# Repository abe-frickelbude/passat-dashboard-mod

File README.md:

# Utilities for the VW Passat (3BG) instrument panel backlight modification project

## adc-serial-monitor

* Written with SpringBoot and Swing
* Provides:
  * A basic "oscilloscope" for AVR ADC input visualization along with some simple signal filtering options
  * A visual controller for RGB(W) programmable LED strips

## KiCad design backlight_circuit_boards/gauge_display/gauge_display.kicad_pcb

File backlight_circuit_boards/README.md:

# Passat 3BG instrument panel backlight circuits

## Center gauge backlight

* Consists of 4x SK6812 RGBW LEDs along with decoupling capacitors
* Custom board, fits existing compartment in the instrument panel's "light mask"
* The DXF file contains the board outline

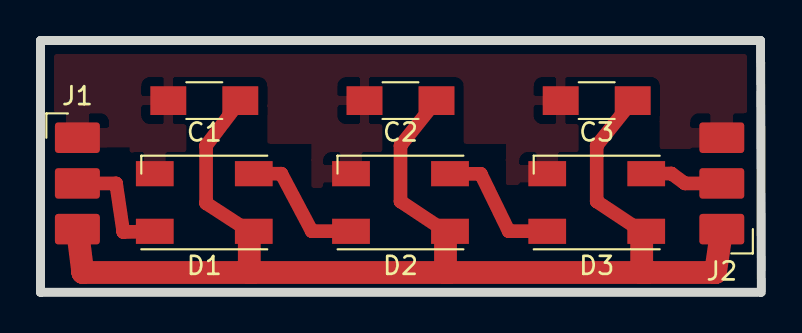
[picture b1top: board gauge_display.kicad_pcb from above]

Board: 2 copper layers, 40.0 x 14.0 mm, 8 parts (0 on the bottom side), 6 nets.

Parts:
C1, C2, C3: C; C_1206_HandSoldering
D1, D2, D3: WS2812B; LED_WS2812B-PLCC4_HandSoldering
J1, J2: Conn_01x03; wire_solder_pads_1x03_2.5x1.7mm_Pitch2.54mm

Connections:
GND: C1.2, C2.2, C3.2, D1.3, D2.3, D3.3, J1.1, J2.3
unnamed: D1.2, D2.4
unnamed: D1.4, J1.2
unnamed: D2.2, D3.4
unnamed: D3.2, J2.2
VCC: C1.1, C2.1, C3.1, D1.1, D2.1, D3.1, J1.3, J2.1

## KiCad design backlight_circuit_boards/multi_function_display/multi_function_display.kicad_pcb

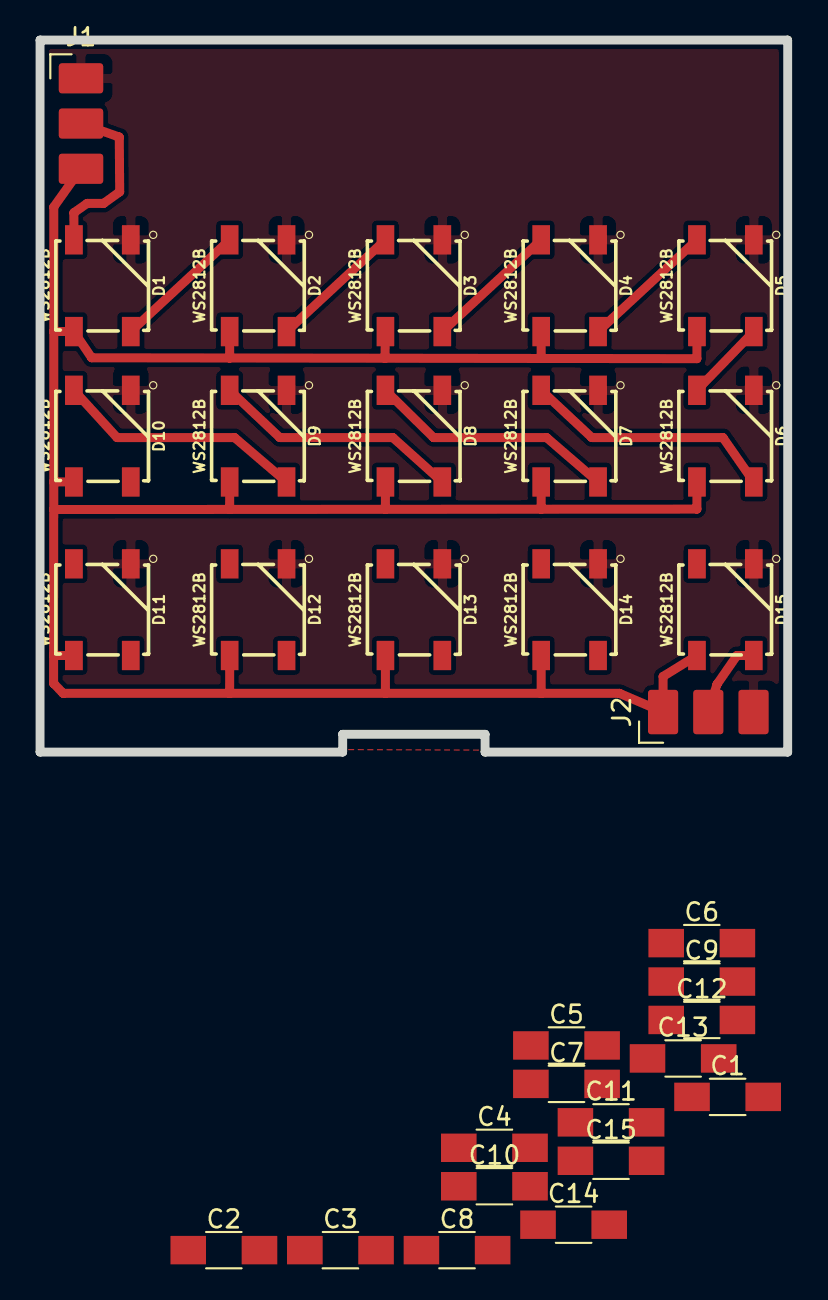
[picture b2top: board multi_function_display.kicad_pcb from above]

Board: 2 copper layers, 42.0 x 40.0 mm, 32 parts (0 on the bottom side), 18 nets.

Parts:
C1, C2, C3, C4, C5, C6, C7, C8, C9, C10, C11, C12, C13, C14, C15: 0.1; C_1206_HandSoldering
D1, D2, D3, D4, D5, D6, D7, D8, D9, D10, D11, D12, D13, D14, D15: WS2812B
J1, J2: Conn_01x03; wire_solder_pads_1x03_2.5x1.7mm_Pitch2.54mm

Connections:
GND: C1.2, C2.2, C3.2, C4.2, C5.2, C6.2, C7.2, C8.2, C9.2, C10.2, C11.2, C12.2, C13.2, C14.2, C15.2, D1.3, D2.3, D3.3, D4.3, D5.3, D6.3, D7.3, D8.3, D9.3, D10.3, D11.3, D12.3, D13.3, D14.3, D15.3, J1.1, J2.3
unnamed: D1.2, D2.4
unnamed: D1.4, J1.2
unnamed: D2.2, D3.4
unnamed: D3.2, D4.4
unnamed: D4.2, D5.4
unnamed: D5.2, D6.4
unnamed: D6.2, D7.4
unnamed: D7.2, D8.4
unnamed: D8.2, D9.4
unnamed: D10.2, D11.4
unnamed: D9.2, D10.4
unnamed: D11.2, D12.4
unnamed: D12.2, D13.4
unnamed: D13.2, D14.4
unnamed: D14.2, D15.4
unnamed: D15.2, J2.2
VCC: C1.1, C2.1, C3.1, C4.1, C5.1, C6.1, C7.1, C8.1, C9.1, C10.1, C11.1, C12.1, C13.1, C14.1, C15.1, D1.1, D2.1, D3.1, D4.1, D5.1, D6.1, D7.1, D8.1, D9.1, D10.1, D11.1, D12.1, D13.1, D14.1, D15.1, J1.3, J2.1

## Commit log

2018-01-07 WIP opamp calculator
2018-01-09 project skeleton
2018-01-09 gitignore
2018-01-09 WIP port of old Kalman filter processing sketch to processing 3.x
    - Maven build is busted right now because the mvn repo "processing-core"
    and "processing-serial" artifacts are messed up, will need to rely on
    local processing 3.x installation instead <sigh...>
2018-01-12 POM corrected to use a local Processing installation
2018-01-13 Forked base code from spring-swing-skeleton, added some dependencies
2018-01-13 Serial port service skeleton
2018-01-14 WIP Serial port parameters dialog
2018-01-21 WIP serial port connectivity
    - POM cleanup
    - Added Ardulink dependency
    - Simplified serial port dialog
    - Moved port name selector into serial port dialog
    - Some experiments with custom icons packs etc.
2018-01-21 Some improvements to window layout code
2018-01-21 WIP arduino uplink
2018-01-25 Migrated to SpringBoot
    - Added some fancy SpringBoot gubbinz
    - WIP: JAnsiTextPane for even moar fancy gubbinz -> support SpringBoot's
    ANSI output in Swing views
    - Window / Controller code: added error message box when no serial ports
    can be detected
2018-01-28 WIP: kustom eqwipment (ansi-color-capable console log pane)
2018-01-30 Fixed some issues
    - autoscrolling now works correctly in JConsoleLogPane / JAnsiTextPane
    - added auto-clear to JConsoleLogPane
    - moved app context instance in the main app class (app context
    reference was being closed prematurely..)
2018-01-31 Minor improvements to GUI code
2018-02-01 Added AdcMonitorViewTest for visualizing various Kalman filter settings
2018-02-03 Basic UI stuff for filter experiments
2018-02-03 Added different filters for further experiments
2018-02-04 Bunch of stuff, working on JColorSwatch custom color picker
2018-02-05 Added ColorSwatchInfoDialog with detailed color information to JColorSwatch
2018-02-05 Basic ZoomableChartView functionality done
    - added color swatches and other controls
2018-02-06 Integrated chart view into main app, working on serial...
2018-02-06 Arduino code for reading ADC over serial link
2018-02-12 Basic ArduLink connection is now operational
2018-02-12 Added filtering and improved refresh rate control
2018-02-13 Basic signal visualization now done
    - added optional pre/post filter thresholding
    - Simple exponential filter seems to be the most suitable, at ~ 0.2
    smoothing factor and ~ 25-30 mV post-filter thresholding operation
2018-02-26 Added separate window for controls and adjusted layout code accordingly
2018-02-26 Added activity tabs and refactored code accordingly
2018-02-27 Added some window min/max/focusing code
2018-02-27 Renamed application to "Arduino Sandbox"
2018-02-27 Renamed base package to "arduino_sandbox"
2018-02-28 WIP RGWB LED color group widget
2018-03-01 WIP: re-working ColorSwatch as proper Swing component
2018-03-03 WIP: LedGroupColorSwatch
2018-03-23 WIP TinyButton
2018-03-24 WIP LedGroupColorSwatch, using new TinyButton/TinyButtonGroup classes
2018-03-26 WIP RgbwSwatchGroup now carries its own layout
2018-03-27 finally fixed the redraw bug in ColorSwatch
2018-03-29 WIP LED group configuration
2018-04-03 WIP config serialization / deserialization
2018-04-05 WIP rotary dial
2018-04-11 WIP: rotary dial
2018-05-11 RangeModel simplified to integer-only operation
2018-05-13 Some package refactoring etc
    - Dial is now basically operational except for change event firing
    - RangeModel renamed to IntegerRangeModel, working fine now
2018-05-13 Dial code cleaned up
2018-05-13 Fixed some rendering bugs in Dial
    - Integrated rotary knobs into RgbwSwatchGroup widget
2018-05-13 Added event handling to RGBW controller and widgets
2018-05-13 WIP RgbwLedMainPanel
2018-05-14 WIP Basic LED sandbox integration
    - load / save configuration completed
    - renamed some classes for better clarity
2018-05-15 Basic scaffold for SK6812 RGBW led strip experimental controller
2018-05-15 test commit to check GIT propah...
2018-05-25 remove obsolete adc-monitor sub-project
2018-05-25 remove obsolete arduino-serial-adc subproject
2018-05-25 Recent Firmata sandbox stuff - Added basic readme.md
2018-05-25 Added VS code workspace config and gitignore
2018-05-26 firmata_ws2812_sandbox project skeleton
2018-05-26 WIP command parser
2018-05-26 Basic custom SysEx message test OK!
2018-05-26 WIP RGBW pixel command
2018-05-27 Basic RGBW controller tests OK, the firmware is roughly operational - WIP pixel positions are inconsistent, trying to figure out why every 2nd pixel is skipped by the firmware!
2018-05-31 Basic LED controller functionality is now operational
2018-06-03 Minor improvements to UI
    - Added change listener to ColorSwatch's color chooser to
    enabled on-the-fly updates to colors while the color chooser
    dialog is still open
    - Removed obsolete JColorSwatch and BiColorSwatch
    - ZoomableChartView migrated to the new ColorSwatch
    - Added manual LED re-init capability to LED control panel
2018-06-10 Create boards
2018-06-10 WIP center gauge backlight circuit board
2018-06-10 Improved copper fill
2018-06-10 Added some workflow documentation
2018-08-05 Added subdirectories, WIP left gauge PCB
2018-08-06 Left gauge PCB done, WIP right gauge PCB, switched to KC 5
2018-08-10 WIP right gauge PCB
2018-08-13 improvements to all boards
2018-09-07 Added gauge clock/km display boards
2018-09-07 Make clock/km board a little smaller, built combined artwork SVG
2018-09-08 Small improvements to thermal relief on all PCBs
2018-09-11 added preliminary design docs (WIP)
2018-11-07 Ported to Java 10 / Spring Boot 2.x
2018-12-23 Switched everything to Firmata (no ArduLink anymore)
    - Added custom message parser & co for retrieving 16-bit ADC values
2018-12-23 Added ADC reads using Firmata
2019-01-11 WIP pulse width compensation sketch
2019-01-12 WIP pulse width compensation simulator
2019-01-19 recent files
2019-01-19 WIP pwm simulator
